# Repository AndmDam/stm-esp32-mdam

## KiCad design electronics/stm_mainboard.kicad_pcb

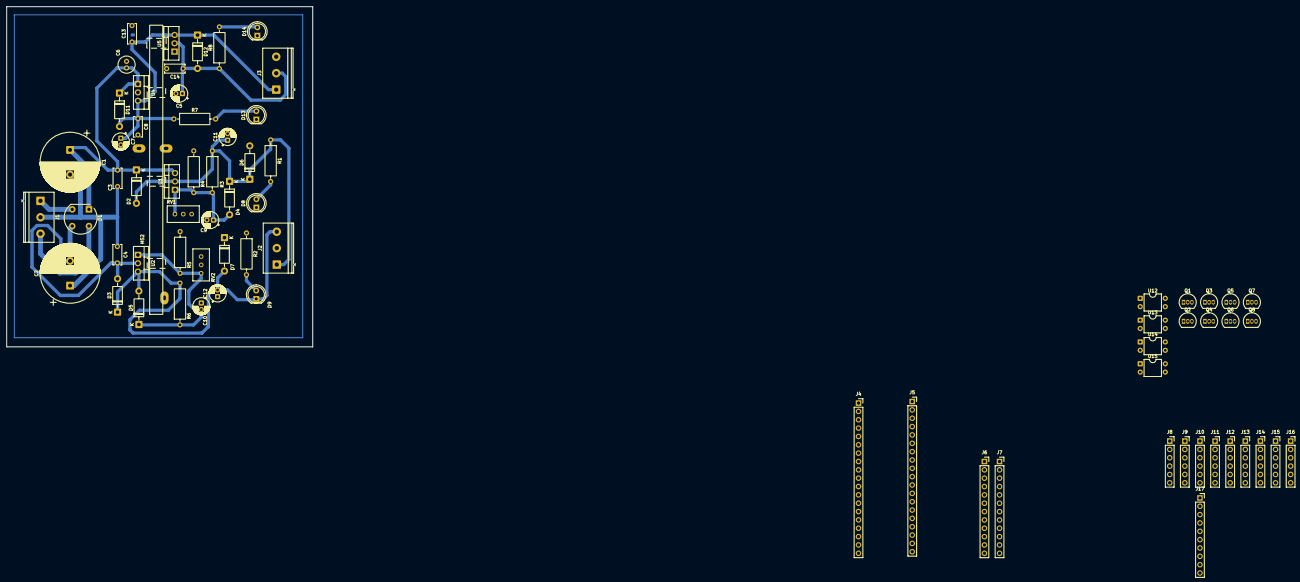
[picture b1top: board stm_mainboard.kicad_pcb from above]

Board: 2 copper layers, 93.2 x 103.5 mm, 75 parts (0 on the bottom side), 44 nets.

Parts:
C1, C2: 4700uF; CP_Radial_D18.0mm_P7.50mm
C3, C4: 100nF; C_Disc_D6.0mm_W2.5mm_P5.00mm
C5: 100uF; CP_Radial_D5.0mm_P2.00mm
C6: 0.22uF; C_Radial_D5.0mm_H11.0mm_P2.00mm
C7, C9, C10, C11, C12: 10uF; CP_Radial_D5.0mm_P2.00mm
C8, C13, C14: 0.1uF; C_Disc_D6.0mm_W2.5mm_P5.00mm
D1: W01G; Diode_Bridge_Round_D9.8mm
D2, D3, D4, D5, D6, D7, D11, D12: 1N4002; D_DO-41_SOD81_P10.16mm_Horizontal
D8: blue_led; LED_D5.0mm
D9: red_led; LED_D5.0mm
D13: Orange_led; LED_D5.0mm
D14: Yellow_led; LED_D5.0mm
H1, H2, H3, H4: MountingHole; MountingHole_3.2mm_M3
HS2: Heatsink_Pad_3Pin; Disipador_4xTO220_Unificado_Reciclado
J1: 17VAC_transformer; TerminalBlock_Phoenix_PT-1,5-3-5.0-H_1x03_P5.00mm_Horizontal
J2: sym_pow_17VDCsupply; TerminalBlock_Phoenix_PT-1,5-3-5.0-H_1x03_P5.00mm_Horizontal
J3: 5VDC-3VDC_GND_out; TerminalBlock_Phoenix_PT-1,5-3-5.0-H_1x03_P5.00mm_Horizontal
J4, J5: Conn_01x19_Socket; PinSocket_1x19_P2.54mm_Vertical
J6, J7: Conn_01x12_Socket; PinSocket_1x12_P2.54mm_Vertical
J8: MCP4725_fine_r1; PinSocket_1x06_P2.54mm_Vertical
J9: MCP4725_coarse_r1; PinSocket_1x06_P2.54mm_Vertical
J10: MCP4725_fine_r2; PinSocket_1x06_P2.54mm_Vertical
J11: MCP4725_coarse_r2; PinSocket_1x06_P2.54mm_Vertical
J12: MCP4725_fine_r3; PinSocket_1x06_P2.54mm_Vertical
J13: MCP4725_coarse_r3; PinSocket_1x06_P2.54mm_Vertical
J14: MCP4725_fine_r4; PinSocket_1x06_P2.54mm_Vertical
J15: MCP4725_coarse_r4; PinSocket_1x06_P2.54mm_Vertical
J16: MCP4725_VBIAS; PinSocket_1x06_P2.54mm_Vertical
J17: ADS1115; PinSocket_1x10_P2.54mm_Vertical
Q1, Q3, Q5, Q7: 2N3904; TO-92_Inline
Q2, Q4, Q6, Q8: 2N3906; TO-92_Inline
R1, R2, R7, R8: 1k; R_Axial_DIN0309_L9.0mm_D3.2mm_P12.70mm_Horizontal
R3, R6: 240; R_Axial_DIN0309_L9.0mm_D3.2mm_P12.70mm_Horizontal
R4, R5: 3.3k; R_Axial_DIN0309_L9.0mm_D3.2mm_P12.70mm_Horizontal
RV1, RV2: 50k; Potentiometer_Bourns_3296W_Vertical
U1: LM317; TO-220-3_Vertical
U2: LM337; TO-220-3_Vertical
U4: LM7805; TO-220-3_Vertical
U5: LM1117T-3.3; TO-220-3_Vertical
U12, U13, U14, U15: PC817; DIP-4_W7.62mm

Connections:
+3.3V: C5.1, C14.1, D12.2 (A), J3.2, R8.1, U5.2 (VO)
+5C: C7.1, C8.1, C13.1, D11.2 (A), D12.1 (K), J3.1, R7.1, U4.3 (VO), U5.3 (VI)
+15V: C11.1, D2.2 (A), D4.1 (K), D6.1 (K), J2.1, R1.1, R3.1, U1.2 (VO)
-15V: C12.2, D3.1 (K), D5.2 (A), D7.2 (A), D9.1 (K), J2.3, R6.2, U2.3 (VO)
/control_digital/+3.3VDC: J4.1, J6.1, J8.5, J9.5, J10.5, J11.5, J12.5, J13.5, J14.5, J15.5, J16.5, J17.1
/control_digital/DGND: J4.14, J5.13, J5.19, J6.2, J8.2, J8.6, J9.2, J9.6, J10.2, J10.6, J11.2, J11.6, J12.2, J12.6, J13.2, J13.6, J14.2, J14.6, J15.2, J15.6, J16.2, J16.6, J17.2, U12.2, U13.2, U14.2, U15.2
/control_digital/SCL_coarse_r1: J6.12, J9.3
/control_digital/SCL_coarse_r2: J7.4, J11.3
/control_digital/SCL_coarse_r3: J7.8, J13.3
/control_digital/SCL_coarse_r4: J7.12, J15.3
/control_digital/SCL_fine_r1: J6.10, J8.3
/control_digital/SCL_fine_r2: J7.2, J10.3
/control_digital/SCL_fine_r3: J7.6, J12.3
/control_digital/SCL_fine_r4: J7.10, J14.3
/control_digital/SCL_main: J5.17, J6.4, J16.3, J17.4
/control_digital/SDA_coarse_r1: J6.11, J9.4
/control_digital/SDA_coarse_r2: J7.3, J11.4
/control_digital/SDA_coarse_r3: J7.7, J13.4
/control_digital/SDA_coarse_r4: J7.11, J15.4
/control_digital/SDA_fine_r1: J6.9, J8.4
/control_digital/SDA_fine_r2: J7.1, J10.4
/control_digital/SDA_fine_r3: J7.5, J12.4
/control_digital/SDA_fine_r4: J7.9, J14.4
/control_digital/SDA_main: J5.15, J6.3, J16.4, J17.3
GND: C1.2, C2.1, C3.2, C4.1, C5.2, C6.2, C7.2, C8.2, C9.2, C10.1, C11.2, C12.1, C13.2, C14.2, D6.2 (A), D7.1 (K), D8.1 (K), D13.1 (K), D14.1 (K), HS2.1, HS2.2, HS2.3, J1.2, J2.2, J3.3, R2.1, R4.2, R5.1, RV1.1, RV1.2, RV2.2, RV2.3, U4.2 (GND), U5.1 (GND)
unnamed: C1.1, C3.1, C6.1, D1.1 (+), D2.1 (K), D11.1 (K), U1.3 (VI), U4.1 (VI)
unnamed: C2.2, C4.2, D1.3 (-), D3.2 (A), U2.2 (VI)
unnamed: C9.1, D4.2 (A), R3.2, R4.1, RV1.3, U1.1 (ADJ)
unnamed: C10.2, D5.1 (K), R5.2, R6.1, RV2.1, U2.1 (ADJ)
unnamed: D8.2 (A), R1.2
unnamed: D9.2 (A), R2.2
unnamed: D13.2 (A), R7.2
unnamed: D14.2 (A), R8.2
unnamed: D1.2, J1.1
unnamed: D1.4, J1.3
unnamed: U12.4, U13.4, U14.4, U15.4
unnamed: Q1.2 (B), Q2.2 (B)
unnamed: Q1.1 (E), Q2.1 (E)
unnamed: Q3.2 (B), Q4.2 (B)
unnamed: Q3.1 (E), Q4.1 (E)
unnamed: Q5.2 (B), Q6.2 (B)
unnamed: Q5.1 (E), Q6.1 (E)
unnamed: Q7.2 (B), Q8.2 (B)
unnamed: Q7.1 (E), Q8.1 (E)

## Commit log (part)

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2026-05-18 Primer commit: Estructura del proyecto
